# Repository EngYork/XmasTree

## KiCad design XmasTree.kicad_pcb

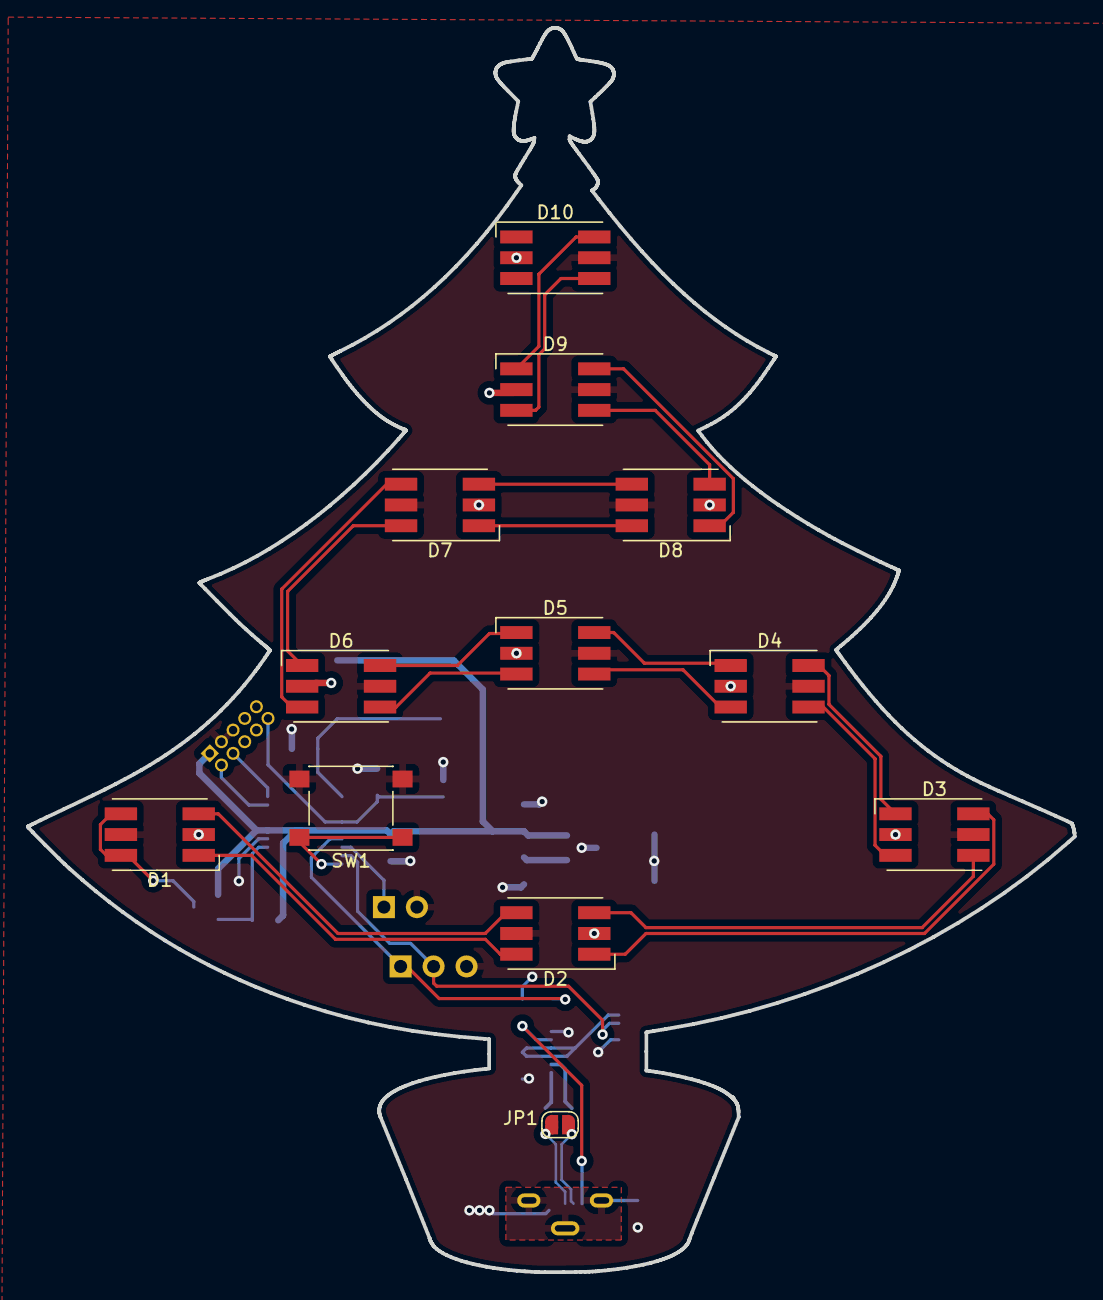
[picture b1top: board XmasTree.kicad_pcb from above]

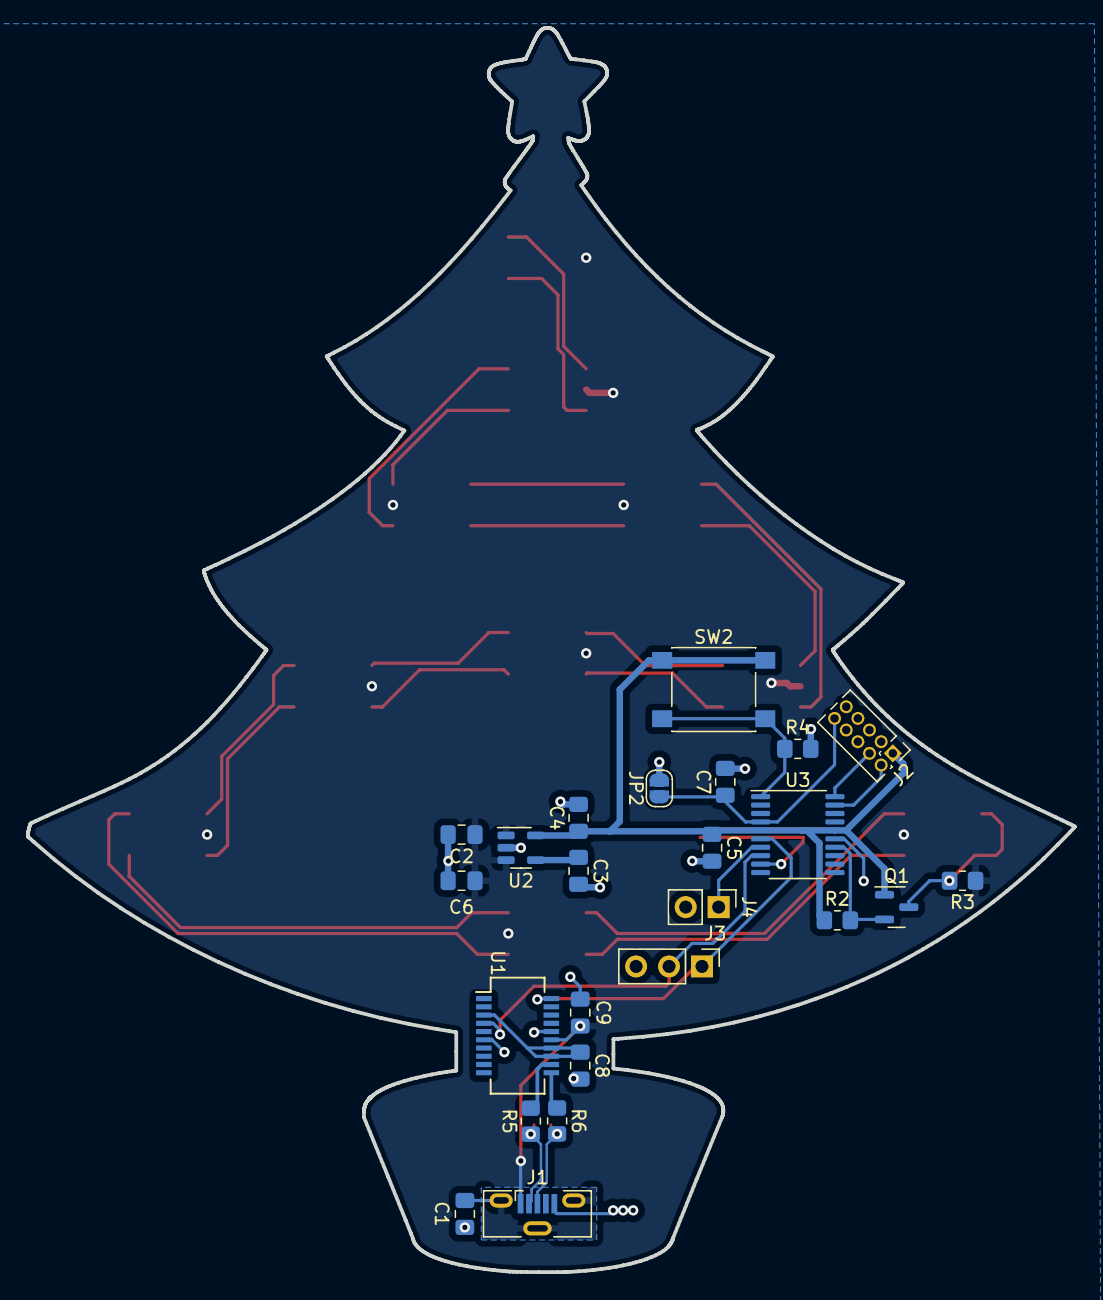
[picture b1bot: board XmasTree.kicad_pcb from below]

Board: 2 copper layers, 80.7 x 95.9 mm, 36 parts (24 on the bottom side), 38 nets.

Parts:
C1, C3, C5, C7, C8: 10n; C_0805_2012Metric_Pad1.18x1.45mm_HandSolder
C2, C4, C9: 1u; C_0805_2012Metric_Pad1.18x1.45mm_HandSolder
C6: 4u7; C_0805_2012Metric_Pad1.18x1.45mm_HandSolder
D1, D2, D3, D4, D5, D6, D7, D8, D9, D10: WS2813B; LED_WS2813_hand
J1: USB_B_Micro; USB_Micro-B_Molex-105133-0001
J2: Conn_ARM_JTAG_SWD_10; PinHeader_2x05_P1.27mm_Vertical
J3: Conn_01x03_Male; PinHeader_1x03_P2.54mm_Vertical
J4: Conn_01x02_Male; PinHeader_1x02_P2.54mm_Vertical
JP1, JP2: SolderJumper_2_Open; SolderJumper-2_P1.3mm_Open_RoundedPad1.0x1.5mm
Q1: BSN20; SOT-23
R2, R3, R4: 10k; R_0805_2012Metric_Pad1.20x1.40mm_HandSolder
R5, R6: 27; R_0805_2012Metric_Pad1.20x1.40mm_HandSolder
SW1, SW2: SW_Push; SW_Push_1P1T_NO_6x6mm_H9.5mm
U1: FT231XS; SSOP-20_3.9x8.7mm_P0.635mm
U2: AP2202K-3.3; SOT-23-5
U3: STM32L011F4Px; TSSOP-20_4.4x6.5mm_P0.65mm

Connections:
+3.3V: C4.1, C5.1, J2.1 (VTref), Q1.1 (G), R2.1, SW2.1, U2.5 (VOUT), U3.5 (VDDA), U3.16 (VDD)
+5V: C2.1, C6.1, C9.1, D1.2 (VCC), D2.2 (VCC), D3.2 (VCC), D4.2 (VCC), D5.2 (VCC), D6.2 (VCC), D7.2 (VCC), D8.2 (VCC), D9.2 (VCC), D10.2 (VCC), J1.1 (VBUS), R3.1, U1.15 (VCC), U2.1 (VIN), U2.3 (EN)
/3v3 MCU/UartRX: J3.1, U1.20 (TXD), U3.6 (PA0)
/3v3 MCU/UartTX: J3.2, U1.4 (RXD), U3.8 (PA2)
/3v3 MCU/btnA: SW1.1, U3.9 (PA3)
/3v3 MCU/rst: C7.1, J2.10 (~RESET), JP2.1 (A), U3.4 (NRST)
/3v3 MCU/swclk: J2.4 (SWDCLK/TCK), U3.20 (PA14)
/3v3 MCU/swdio: J2.2 (SWDIO/TMS), U3.19 (PA13)
/UsbD+: J1.3 (D+), JP1.1 (A), R6.2
/UsbD-: J1.2 (D-), JP1.2 (B), R5.1
/neopixel string/pxCtrl: D1.4 (DIN), D1.6 (BIN), Q1.3 (D), R3.2
/pxCtrlLV: Q1.2 (S), R2.2, U3.14 (PB1)
GND: C1.2, C2.2, C3.2, C4.2, C5.2, C6.2, C7.2, C8.2, C9.2, D1.5 (GND), D2.5 (GND), D3.5 (GND), D4.5 (GND), D5.5 (GND), D6.5 (GND), D7.5 (GND), D8.5 (GND), D9.5 (GND), D10.5 (GND), J1.5 (GND), J2.3 (GND), J2.5 (GND), J3.3, J4.2, JP2.2 (B), R4.2, SW1.2, U1.6 (GND), U1.16 (GND), U2.2 (GND), U3.15 (VSS)
unnamed: C1.1, J1.6 (Shield)
unnamed: C3.1, U2.4 (ADJ)
unnamed: D1.1 (BO), D2.6 (BIN)
unnamed: D1.3 (DOUT), D2.4 (DIN)
unnamed: D2.1 (BO), D3.6 (BIN)
unnamed: D2.3 (DOUT), D3.4 (DIN)
unnamed: D3.1 (BO), D4.6 (BIN)
unnamed: D3.3 (DOUT), D4.4 (DIN)
unnamed: D4.1 (BO), D5.6 (BIN)
unnamed: D4.3 (DOUT), D5.4 (DIN)
unnamed: D5.1 (BO), D6.6 (BIN)
unnamed: D5.3 (DOUT), D6.4 (DIN)
unnamed: D6.1 (BO), D7.6 (BIN)
unnamed: D6.3 (DOUT), D7.4 (DIN)
unnamed: D7.1 (BO), D8.6 (BIN)
unnamed: D7.3 (DOUT), D8.4 (DIN)
unnamed: D8.1 (BO), D9.6 (BIN)
unnamed: D8.3 (DOUT), D9.4 (DIN)
unnamed: D9.3 (DOUT), D10.4 (DIN)
unnamed: D9.1 (BO), D10.6 (BIN)
unnamed: J4.1, U3.7 (PA1)
unnamed: R4.1, SW2.2, U3.1 (PB9)
unnamed: R6.1, U1.11 (USBDP)
unnamed: R5.2, U1.12 (USBDM)
unnamed: C8.1, U1.3 (VCCIO), U1.13 (3V3OUT), U1.14 (~RESET)

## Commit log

2022-11-05 Import pumkpin schematic base
2022-11-05 Swap FT231XQ for FT231XS
2022-11-05 Import xmas tree outline in pcb
2022-11-06 Start laying out pcb
2022-11-06 RC 1
2022-11-10 Review. Set USB as differential pair. Implemented USB-UART as in Data Sheet application circuit.
2022-11-21 Gitignore. Housekeeping
